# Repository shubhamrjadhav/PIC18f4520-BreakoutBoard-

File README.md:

# PIC18f4520-BreakoutBoard-
EAGLE design to create simple projects with PIC18f4520

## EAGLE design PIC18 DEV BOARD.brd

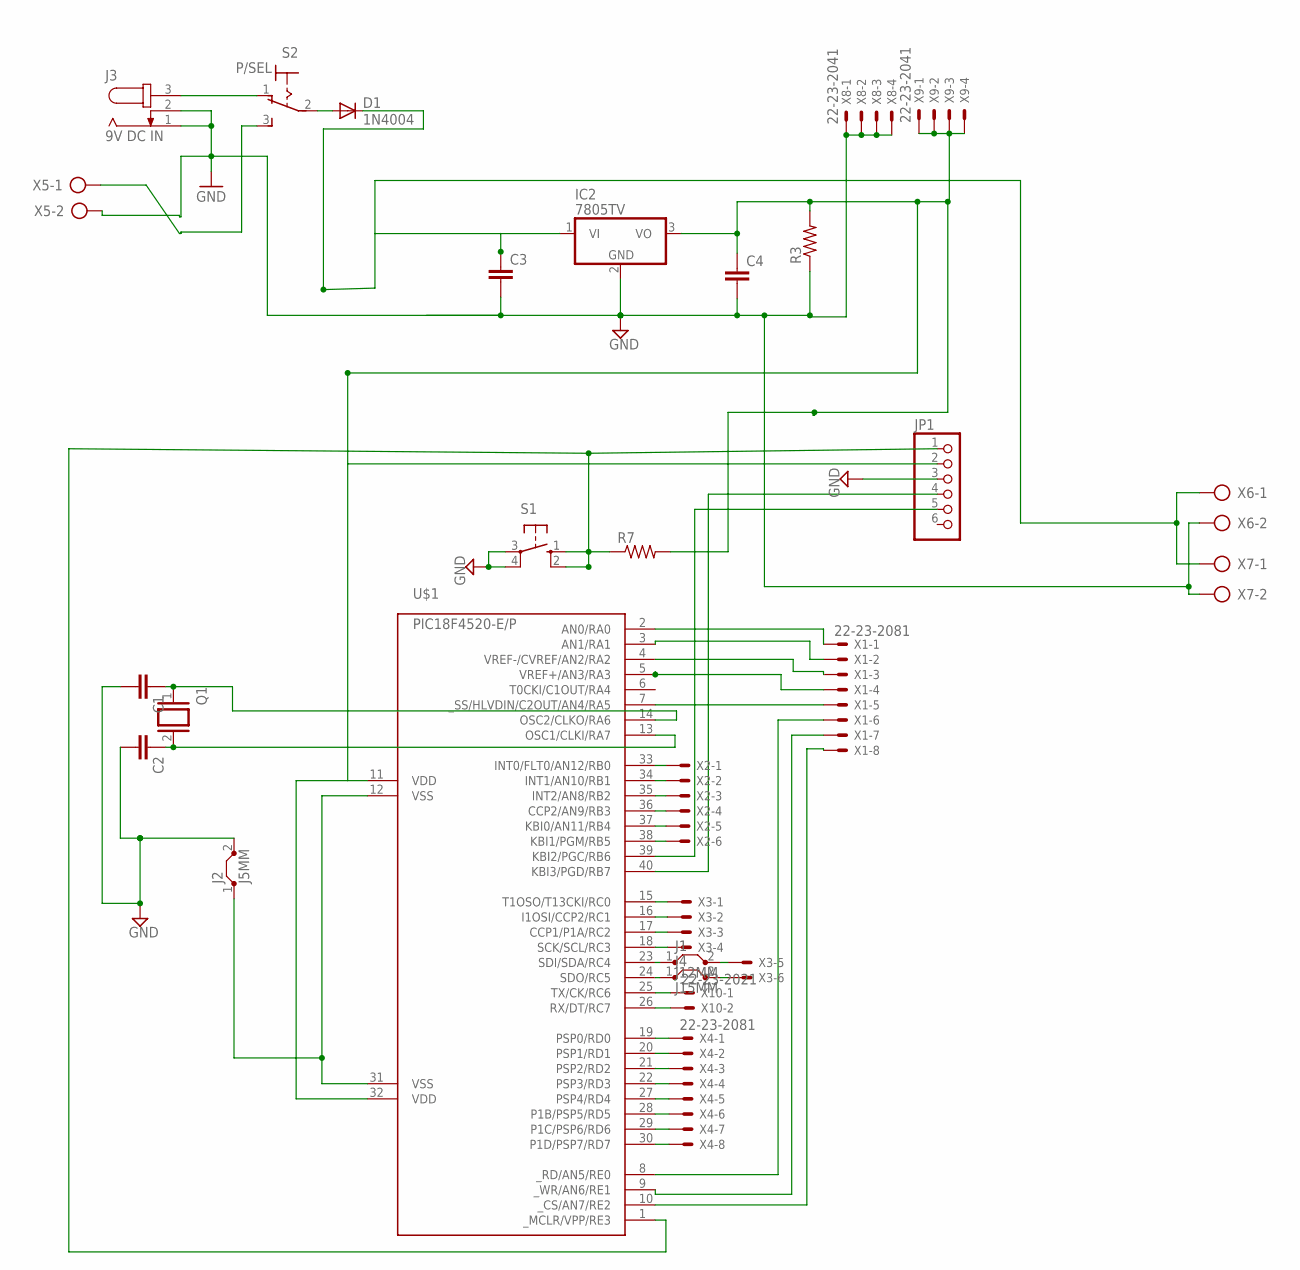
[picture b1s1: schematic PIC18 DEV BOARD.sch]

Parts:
C1, C2, C3, C4: C-EU025-025X050; C025-025X050
D1: 1N4004; DO41-10; MPN 1N4004
IC2: 7805TV; TO220V
J1: J12MM; 12
J2: J5MM; 05
J3: 9V DC IN; SPC4077; MPN RAPC722X
J4: J15MM; 15
JP1: PINHD-1X6; 1X06
Q1: XTAL/S; QS
R3, R7: R-US_0207/10; 0207/10
S1: 10-XX; B3F-10XX
S2: P/SEL; 320-916; MPN 5636A9
U$1: PIC18F4520-E/P; DIL40
X1, X4: 22-23-2081
X2, X3: 22-23-2061
X5, X6, X7: AK500/2-H
X8, X9: 22-23-2041
X10: 22-23-2021

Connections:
GND: C1.2, C2.2, C3.2, C4.2, IC2.2 (GND), J2.2, J3.1, J3.2, JP1.3, R3.1, S1.3, S1.4 (P1), X5.2, X6.2, X7.2, X8.1, X8.2, X8.3, X8.4
unnamed: JP1.1, R7.1, S1.1 (S), S1.2 (S1), U$1.1 (_MCLR/VPP/RE3)
unnamed: U$1.2 (AN0/RA0), X1.1
unnamed: U$1.3 (AN1/RA1), X1.2
unnamed: U$1.4 (VREF-/CVREF/AN2/RA2), X1.3
unnamed: J3.3, S2.1 (O)
unnamed: U$1.7 (_SS/HLVDIN/C2OUT/AN4/RA5), X1.5
unnamed: U$1.33 (INT0/FLT0/AN12/RB0), X2.1
unnamed: U$1.34 (INT1/AN10/RB1), X2.2
unnamed: U$1.35 (INT2/AN8/RB2), X2.3
unnamed: U$1.36 (CCP2/AN9/RB3), X2.4
unnamed: U$1.37 (KBI0/AN11/RB4), X2.5
unnamed: U$1.38 (KBI1/PGM/RB5), X2.6
unnamed: U$1.15 (T1OSO/T13CKI/RC0), X3.1
unnamed: U$1.16 (I1OSI/CCP2/RC1), X3.2
unnamed: U$1.17 (CCP1/P1A/RC2), X3.3
unnamed: U$1.18 (SCK/SCL/RC3), X3.4
unnamed: J1.1, U$1.23 (SDI/SDA/RC4)
unnamed: J4.1, U$1.24 (SDO/RC5)
unnamed: U$1.25 (TX/CK/RC6), X10.1
unnamed: J2.1, U$1.12 (VSS), U$1.31 (VSS)
unnamed: C1.1, Q1.1, U$1.14 (OSC2/CLKO/RA6)
unnamed: C2.1, Q1.2, U$1.13 (OSC1/CLKI/RA7)
unnamed: U$1.26 (RX/DT/RC7), X10.2
unnamed: U$1.19 (PSP0/RD0), X4.1
unnamed: U$1.20 (PSP1/RD1), X4.2
unnamed: U$1.21 (PSP2/RD2), X4.3
unnamed: U$1.22 (PSP3/RD3), X4.4
unnamed: J1.2, X3.5
unnamed: JP1.4, U$1.40 (KBI3/PGD/RB7)
unnamed: JP1.5, U$1.39 (KBI2/PGC/RB6)
unnamed: U$1.27 (PSP4/RD4), X4.5
unnamed: U$1.28 (P1B/PSP5/RD5), X4.6
unnamed: U$1.29 (P1C/PSP6/RD6), X4.7
unnamed: U$1.30 (P1D/PSP7/RD7), X4.8
unnamed: U$1.8 (_RD/AN5/RE0), X1.6
unnamed: U$1.9 (_WR/AN6/RE1), X1.7
unnamed: U$1.10 (_CS/AN7/RE2), X1.8
unnamed: U$1.5 (VREF+/AN3/RA3), X1.4
unnamed: J4.2, X3.6
unnamed: D1.A, S2.2
unnamed: C3.1, D1.C, IC2.1 (VI), X6.1, X7.1
unnamed: S2.3 (S), X5.1
unnamed: C4.1, IC2.3 (VO), JP1.2, R3.2, R7.2, U$1.11 (VDD), U$1.32 (VDD), X9.1, X9.2, X9.3, X9.4

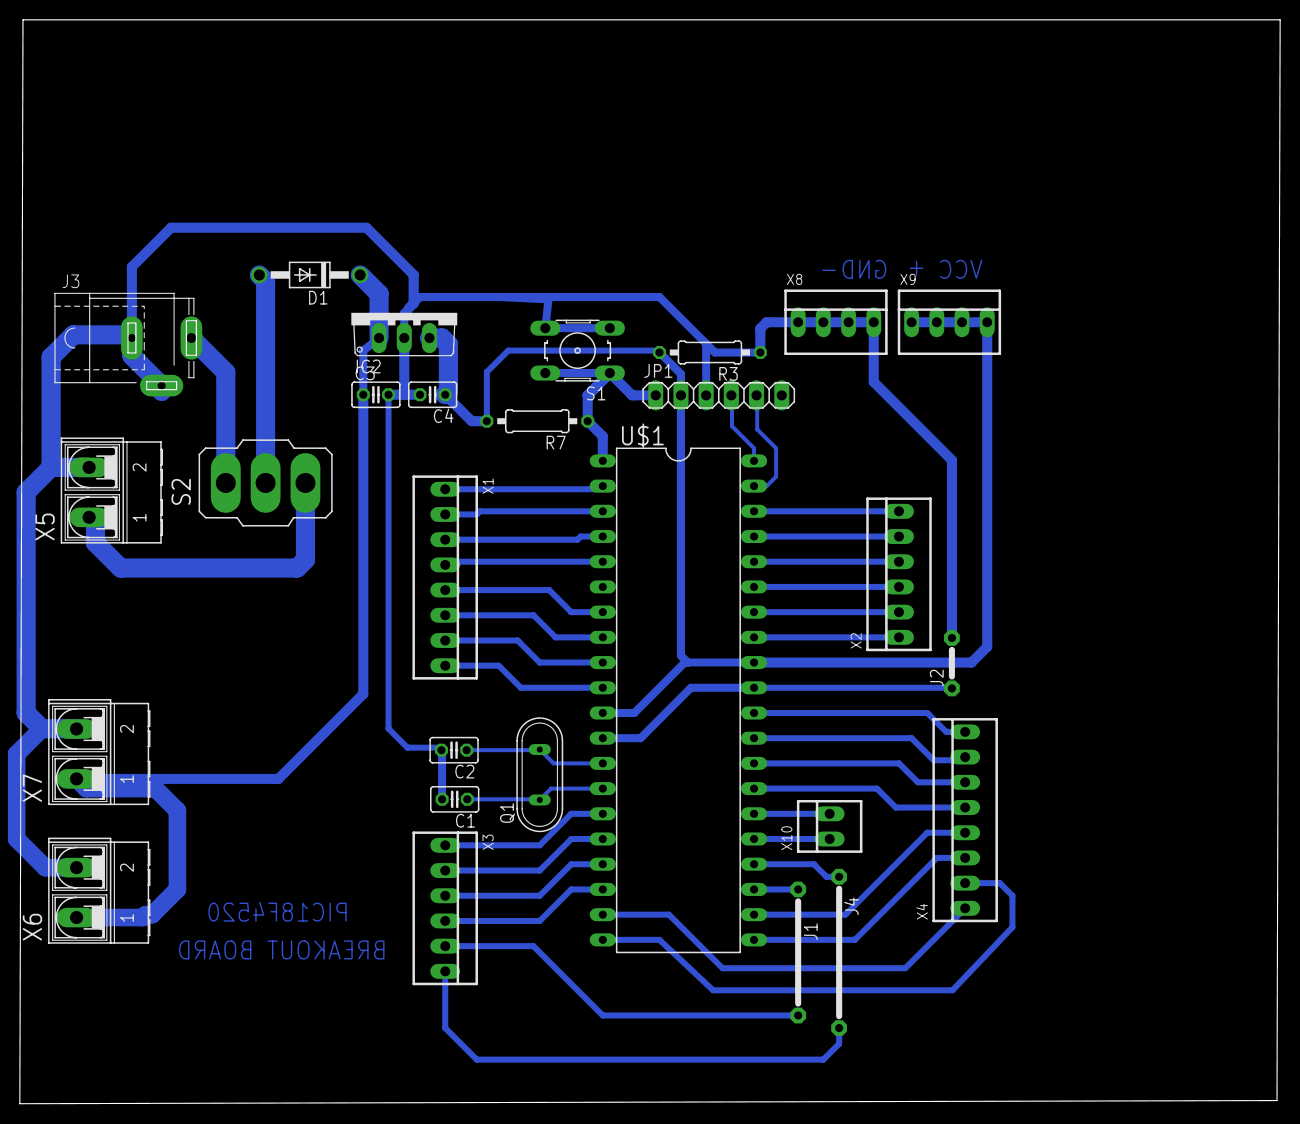
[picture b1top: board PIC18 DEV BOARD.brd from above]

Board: 2 copper layers, 127.0 x 109.2 mm, 27 parts (0 on the bottom side), 44 nets.

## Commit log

2018-02-10 Use typical value resistor and capacitor and crystal as per applications
